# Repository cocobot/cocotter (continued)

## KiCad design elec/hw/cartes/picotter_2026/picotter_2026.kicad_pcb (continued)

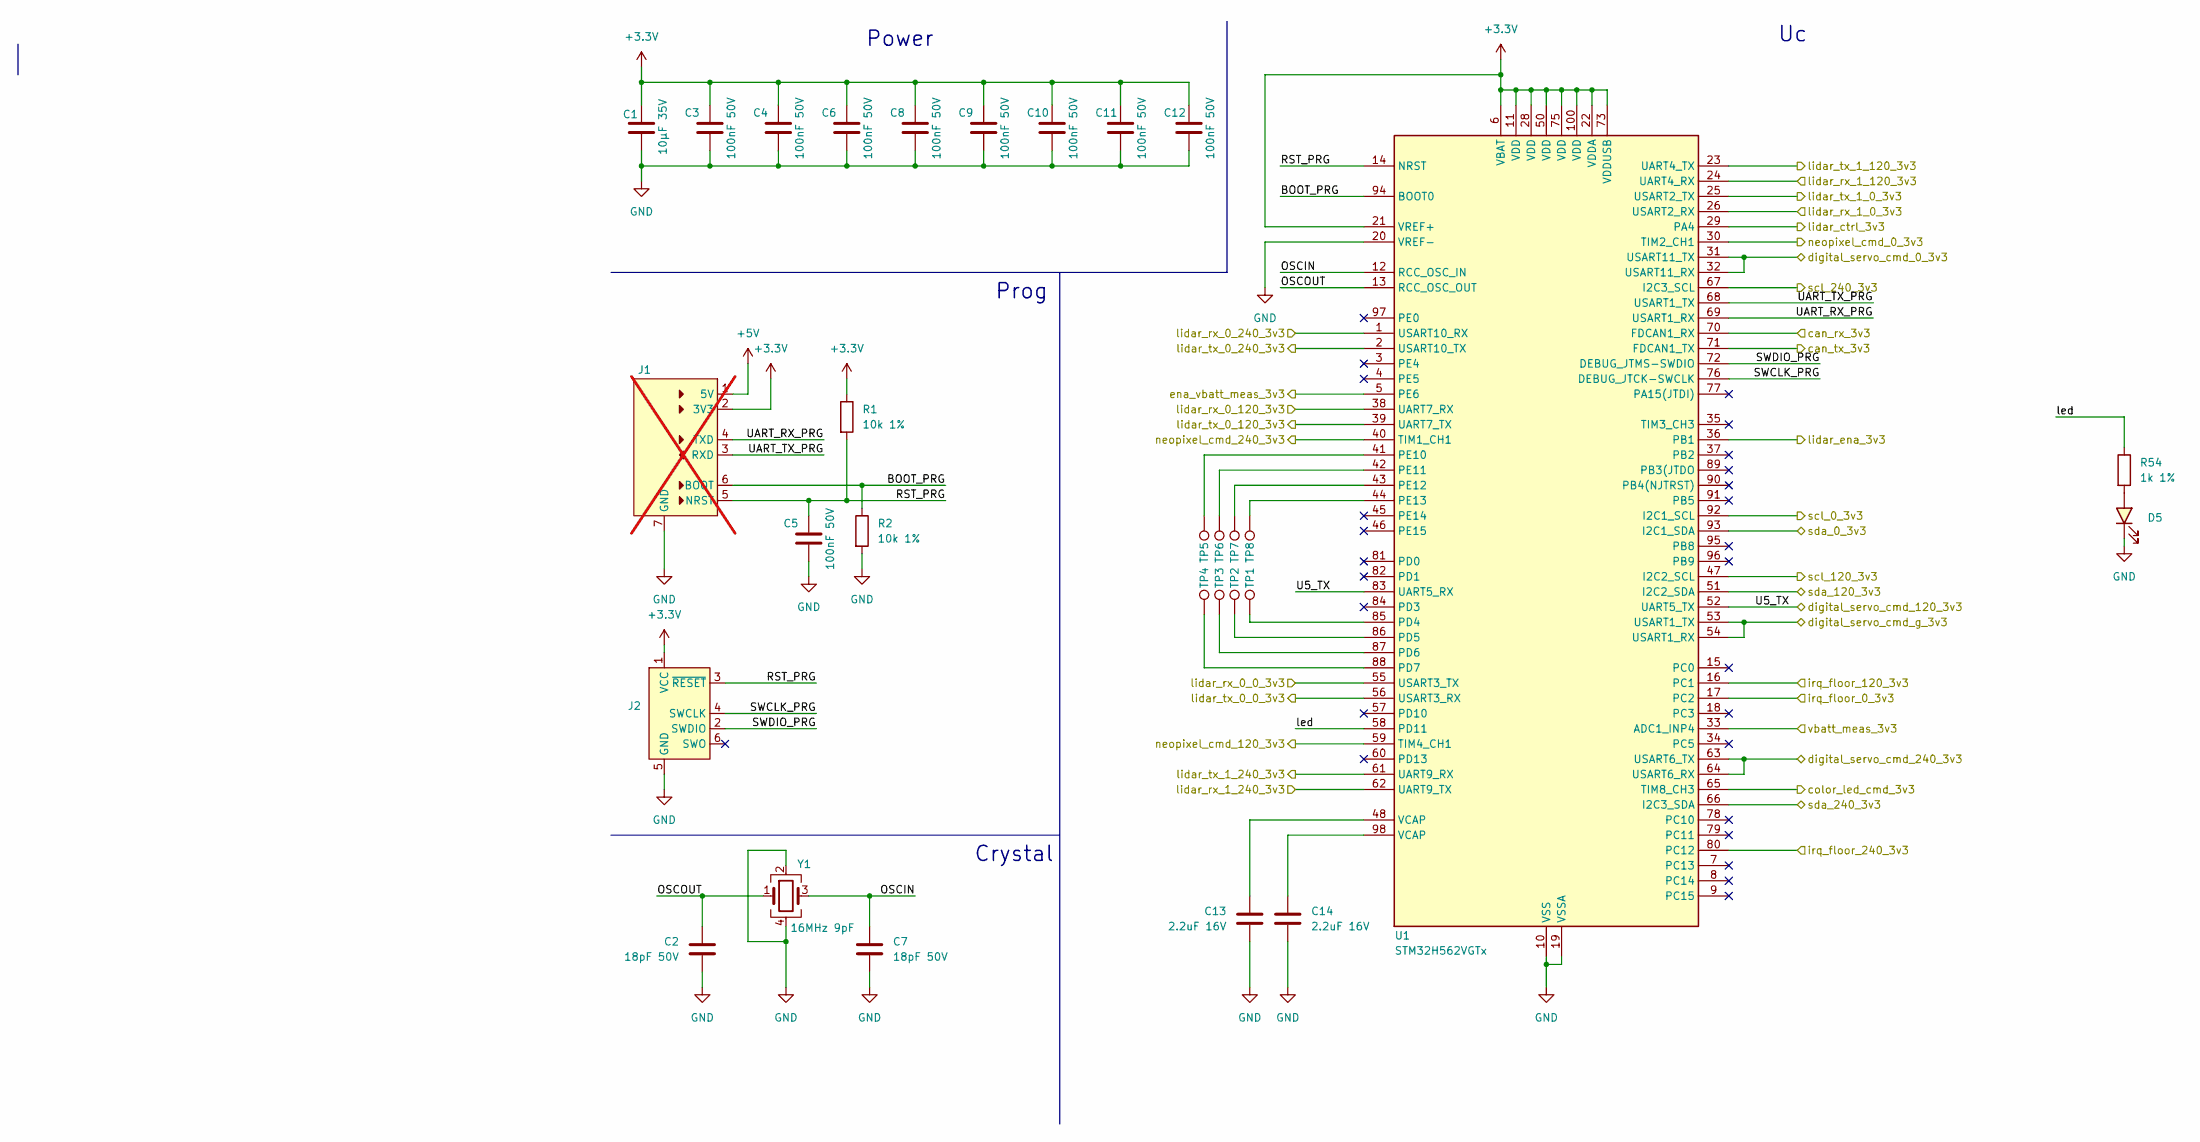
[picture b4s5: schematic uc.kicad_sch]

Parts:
C1: 10µF 35V; C_1206_3216Metric; jlcpcb C454102
C2, C7: 18pF 50V; C_0603_1608Metric; JLCPCB Part # C5137620
C3, C4, C5, C6, C8, C9, C10, C11, C12: 100nF 50V; C_0603_1608Metric; JLCPCB Part # C14663
C13, C14: 2.2uF 16V; C_0603_1608Metric; JLCPCB Part # C23630
D5: green, 0603; LED_0603_1608Metric; DIGIKEY_REF 3147-B19Y1UYG-20C000313U1930CT-ND
J1: eps32_uart_programmer; JLCPCB Part # C492406; not fitted
J2: Conn_ARM_SWD_TagConnect_TC2030; Tag-Connect_TC2030-IDC-FP_2x03_P1.27mm_Vertical
R1, R2: 10k 1%; r0603_reflow; mouser 603-RC0603FR-10100KL
R54: 1k 1%; r0603_reflow; mouser 603-RC0603FR-10100KL
TP1, TP2, TP3, TP4, TP5, TP6, TP7, TP8: TestPoint; testpoint-THT-0.5mm
U1: STM32H562VGTx; LQFP-100_14x14mm_P0.5mm
Y1: 16MHz 9pF; Crystal_SMD_3225-4Pin_3.2x2.5mm; JLCPCB Part # C13738

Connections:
+3.3V: C1.1, C3.1, C4.1, C6.1, C8.1, C9.1, C10.1, C11.1, C12.1, J1.2 (3V3), J2.1 (VCC), R1.1, U1.6 (VBAT), U1.11 (VDD), U1.21 (VREF+), U1.22 (VDDA), U1.28 (VDD), U1.50 (VDD), U1.73 (VDDUSB), U1.75 (VDD), U1.100 (VDD); also elsewhere on the board
+5V: J1.1 (5V); also elsewhere on the board
/Side 0/color_led_cmd_3v3: U1.65 (TIM8_CH3); also elsewhere on the board
/Side 0/digital_servo_cmd_3v3: U1.31 (USART11_TX), U1.32 (USART11_RX); also elsewhere on the board
/Side 0/digital_servo_cmd_g_3v3: U1.53 (USART1_TX), U1.54 (USART1_RX); also elsewhere on the board
/Side 0/irq_floor_3v3: U1.17 (PC2); also elsewhere on the board
/Side 0/lidar_ctrl_3v3: U1.29 (PA4); also elsewhere on the board
/Side 0/lidar_rx_0_3v3: U1.55 (USART3_TX); also elsewhere on the board
/Side 0/lidar_rx_1_3v3: U1.26 (USART2_RX); also elsewhere on the board
/Side 0/lidar_tx_0_3v3: U1.56 (USART3_RX); also elsewhere on the board
/Side 0/lidar_tx_1_3v3: U1.25 (USART2_TX); also elsewhere on the board
/Side 0/neopixel_cmd_3v3: U1.30 (TIM2_CH1); also elsewhere on the board
/Side 0/scl_3v3: U1.92 (I2C1_SCL); also elsewhere on the board
/Side 0/sda_3v3: U1.93 (I2C1_SDA); also elsewhere on the board
/Side 120/digital_servo_cmd_3v3: U1.52 (UART5_TX), U1.83 (UART5_RX); also elsewhere on the board
/Side 120/irq_floor_3v3: U1.16 (PC1); also elsewhere on the board
/Side 120/lidar_rx_0_3v3: U1.38 (UART7_RX); also elsewhere on the board
/Side 120/lidar_rx_1_3v3: U1.24 (UART4_RX); also elsewhere on the board
/Side 120/lidar_tx_0_3v3: U1.39 (UART7_TX); also elsewhere on the board
/Side 120/lidar_tx_1_3v3: U1.23 (UART4_TX); also elsewhere on the board
/Side 120/neopixel_cmd_3v3: U1.59 (TIM4_CH1); also elsewhere on the board
/Side 120/scl_3v3: U1.47 (I2C2_SCL); also elsewhere on the board
/Side 120/sda_3v3: U1.51 (I2C2_SDA); also elsewhere on the board
/Side 240/digital_servo_cmd_3v3: U1.63 (USART6_TX), U1.64 (USART6_RX); also elsewhere on the board
/Side 240/irq_floor_3v3: U1.80 (PC12); also elsewhere on the board
/Side 240/lidar_rx_0_3v3: U1.1 (USART10_RX); also elsewhere on the board
/Side 240/lidar_rx_1_3v3: U1.62 (UART9_TX); also elsewhere on the board
/Side 240/lidar_tx_0_3v3: U1.2 (USART10_TX); also elsewhere on the board
/Side 240/lidar_tx_1_3v3: U1.61 (UART9_RX); also elsewhere on the board
/Side 240/neopixel_cmd_3v3: U1.40 (TIM1_CH1); also elsewhere on the board
/Side 240/scl_3v3: U1.67 (I2C3_SCL); also elsewhere on the board
/Side 240/sda_3v3: U1.66 (I2C3_SDA); also elsewhere on the board
/com/can_rx_3v3: U1.70 (FDCAN1_RX); also elsewhere on the board
/com/can_tx_3v3: U1.71 (FDCAN1_TX); also elsewhere on the board
/power/ena_vbatt_meas_3v3: U1.5 (PE6); also elsewhere on the board
/power/lidar_ena_3v3: U1.36 (PB1); also elsewhere on the board
/power/vbatt_meas_3v3: U1.33 (ADC1_INP4); also elsewhere on the board
/uc/BOOT_PRG: J1.6 (BOOT), R2.1, U1.94 (BOOT0)
/uc/OSCIN: C7.1, U1.12 (RCC_OSC_IN), Y1.3
/uc/OSCOUT: C2.1, U1.13 (RCC_OSC_OUT), Y1.1
/uc/RST_PRG: C5.1, J1.5 (NRST), J2.3 (~RESET), R1.2, U1.14 (NRST)
/uc/SWCLK_PRG: J2.4 (SWCLK), U1.76 (DEBUG_JTCK-SWCLK)
/uc/SWDIO_PRG: J2.2 (SWDIO), U1.72 (DEBUG_JTMS-SWDIO)
/uc/UART_RX_PRG: J1.4 (TXD), U1.69 (USART1_RX)
/uc/UART_TX_PRG: J1.3 (RXD), U1.68 (USART1_TX)
/uc/led: R54.1, U1.58 (PD11)
GND: C1.2, C2.2, C3.2, C4.2, C5.2, C6.2, C7.2, C8.2, C9.2, C10.2, C11.2, C12.2, C13.2, C14.2, D5.C, J1.7 (GND), J2.5 (GND), R2.2, U1.10 (VSS), U1.19 (VSSA), U1.20 (VREF-), U1.27 (VSS), U1.49 (VSS), U1.74 (VSS), U1.99 (VSS), Y1.2, Y1.4; also elsewhere on the board
unnamed: C13.1, U1.48 (VCAP)
unnamed: C14.1, U1.98 (VCAP)
unnamed: D5.A, R54.2
unnamed: TP1.1, U1.85 (PD4)
unnamed: TP2.1, U1.86 (PD5)
unnamed: TP3.1, U1.87 (PD6)
unnamed: TP4.1, U1.88 (PD7)
unnamed: TP5.1, U1.41 (PE10)
unnamed: TP6.1, U1.42 (PE11)
unnamed: TP7.1, U1.43 (PE12)
unnamed: TP8.1, U1.44 (PE13)

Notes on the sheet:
Prog
Crystal
Power

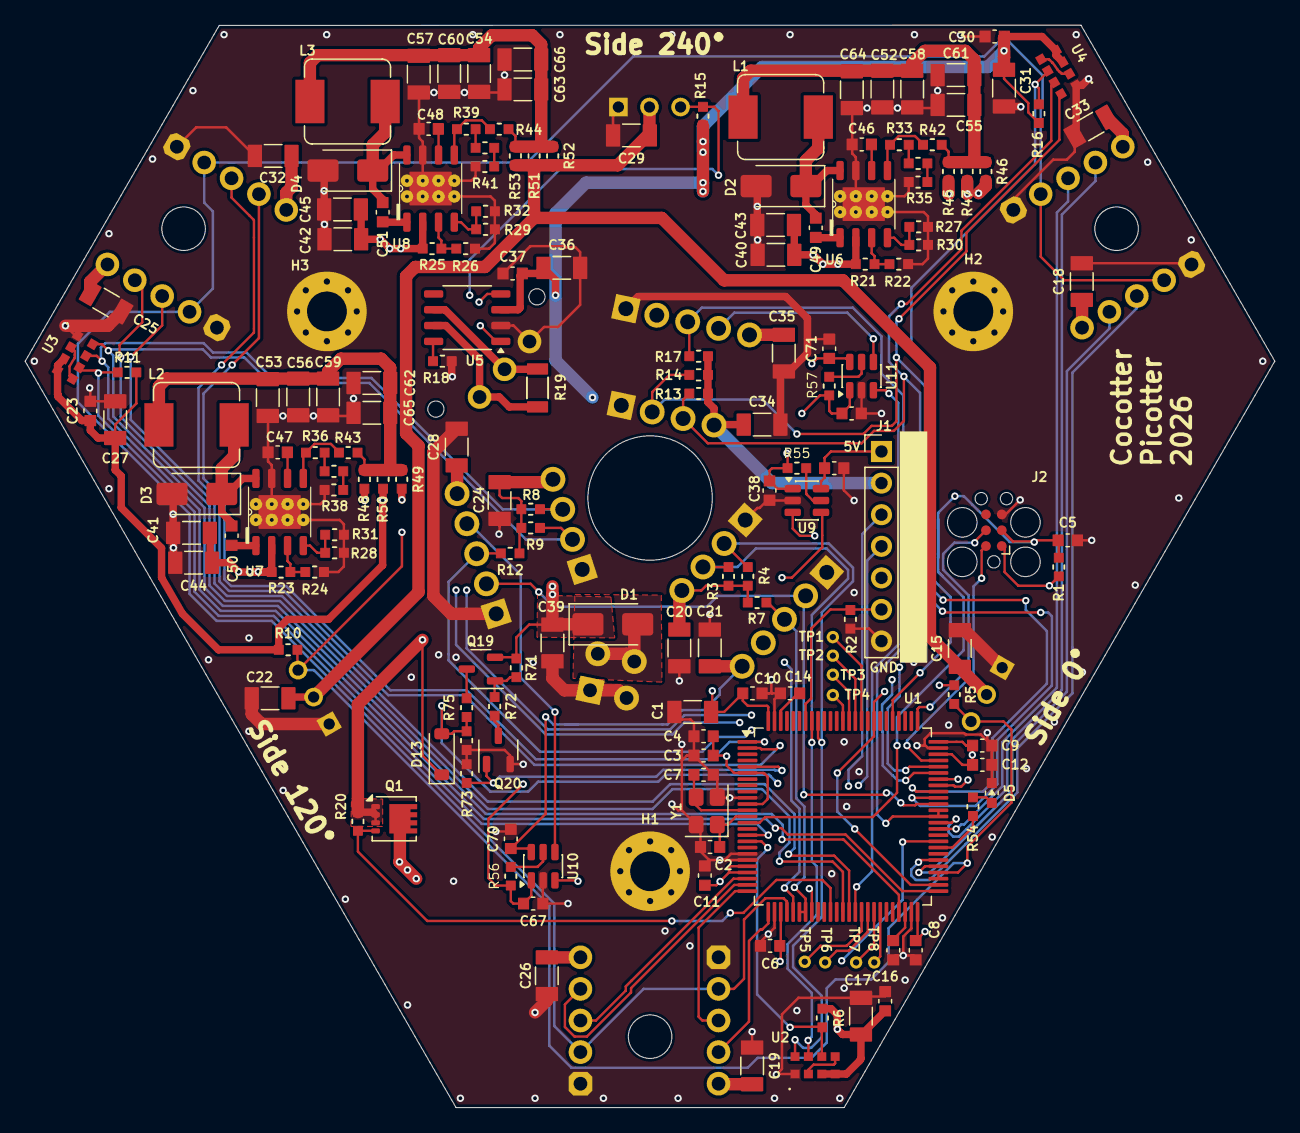
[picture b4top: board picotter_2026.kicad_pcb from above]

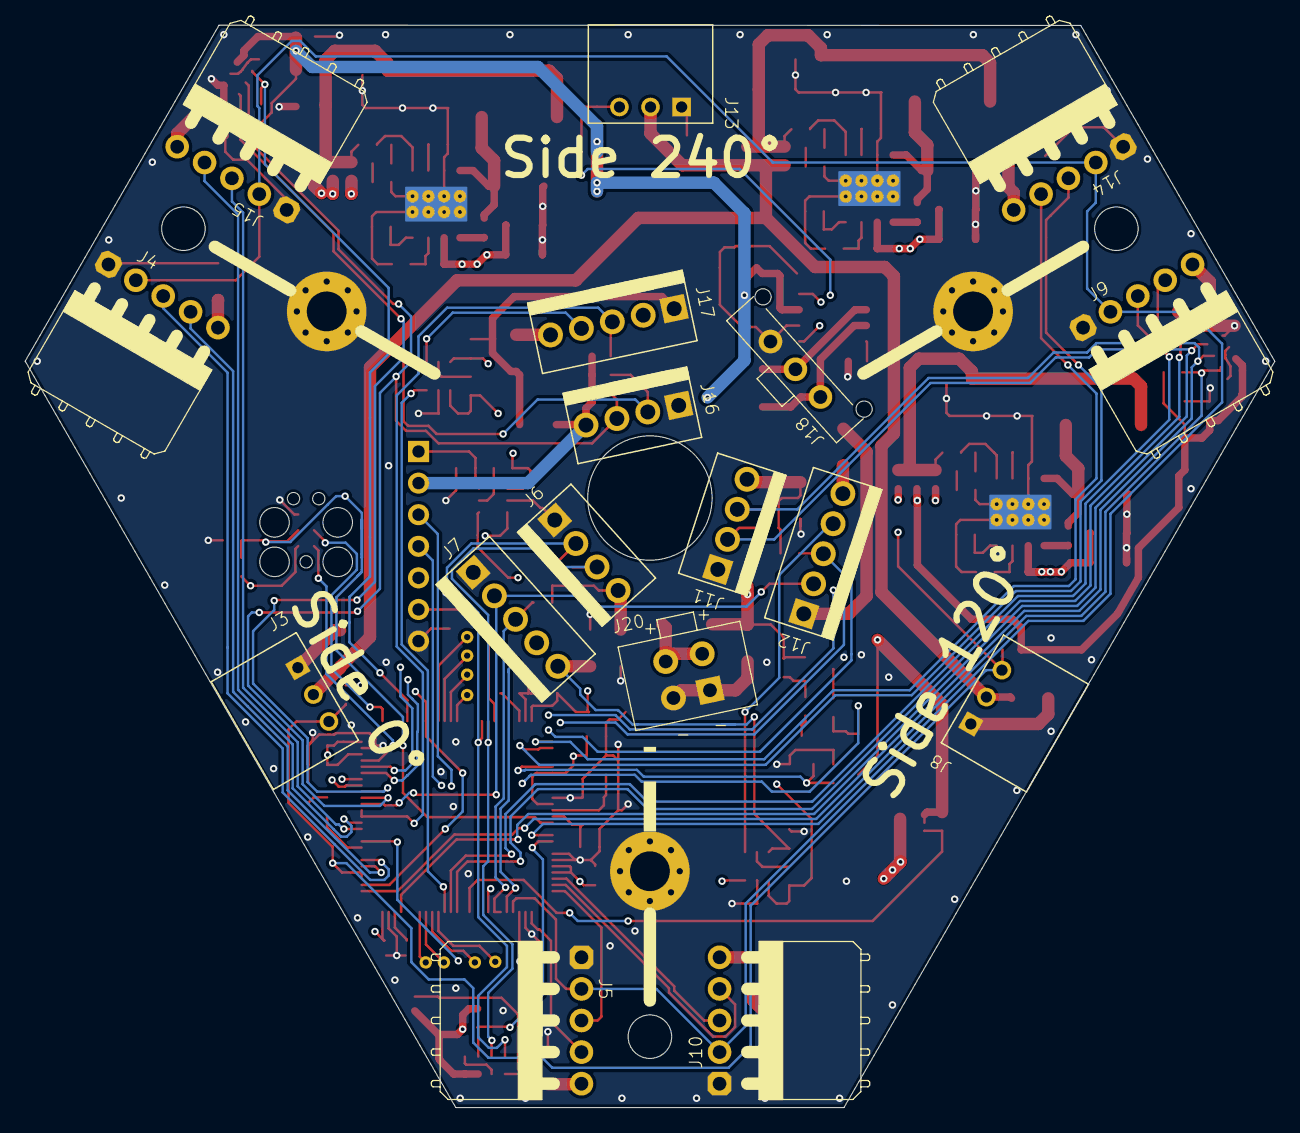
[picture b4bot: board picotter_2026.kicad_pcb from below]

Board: 4 copper layers, 100.5 x 87.0 mm, 187 parts (17 on the bottom side), 104 nets.

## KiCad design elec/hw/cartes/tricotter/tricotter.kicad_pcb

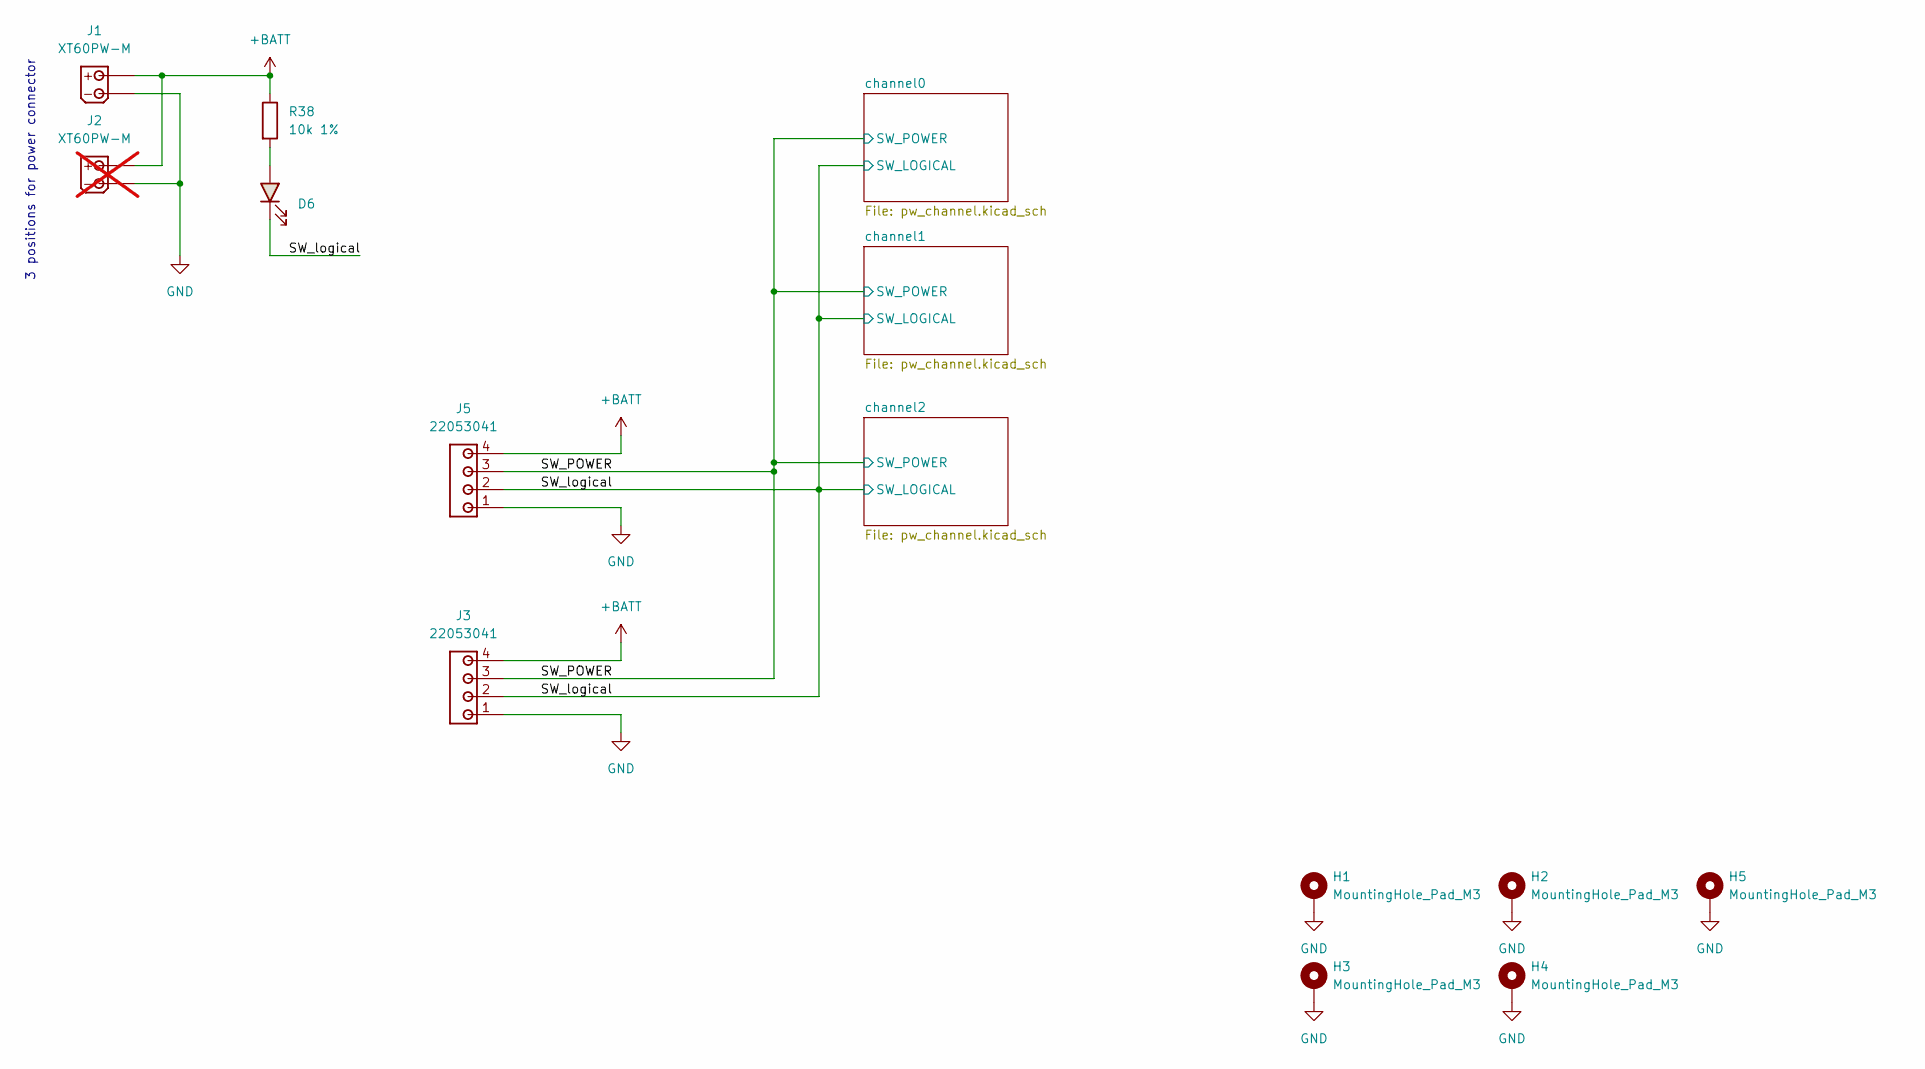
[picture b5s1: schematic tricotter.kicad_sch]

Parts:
D6: white, 0603; LED_0603_1608Metric; JLCPCB Part # C2290
H1, H2, H3, H4, H5: MountingHole_Pad_M3; MountingHole_3.2mm_M3_Pad_Via
J1: XT60PW-M; JLCPCB Part # C98732
J2: XT60PW-M; JLCPCB Part # C98732; not fitted
J3, J5: 22053041; JLCPCB Part # C5271241
R38: 10k 1%; r0603_reflow; mouser 603-RC0603FR-10100KL

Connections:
+BATT: J1.P, J2.P, J3.4, J5.4, R38.1; also elsewhere on the board
/SW_POWER: J3.3, J5.3; also elsewhere on the board
/SW_logical: D6.C, J3.2, J5.2; also elsewhere on the board
GND: H1.1, H2.1, H3.1, H4.1, H5.1, J1.M, J2.M, J3.1, J5.1; also elsewhere on the board
unnamed: D6.A, R38.2

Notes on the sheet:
3 positions for power connector

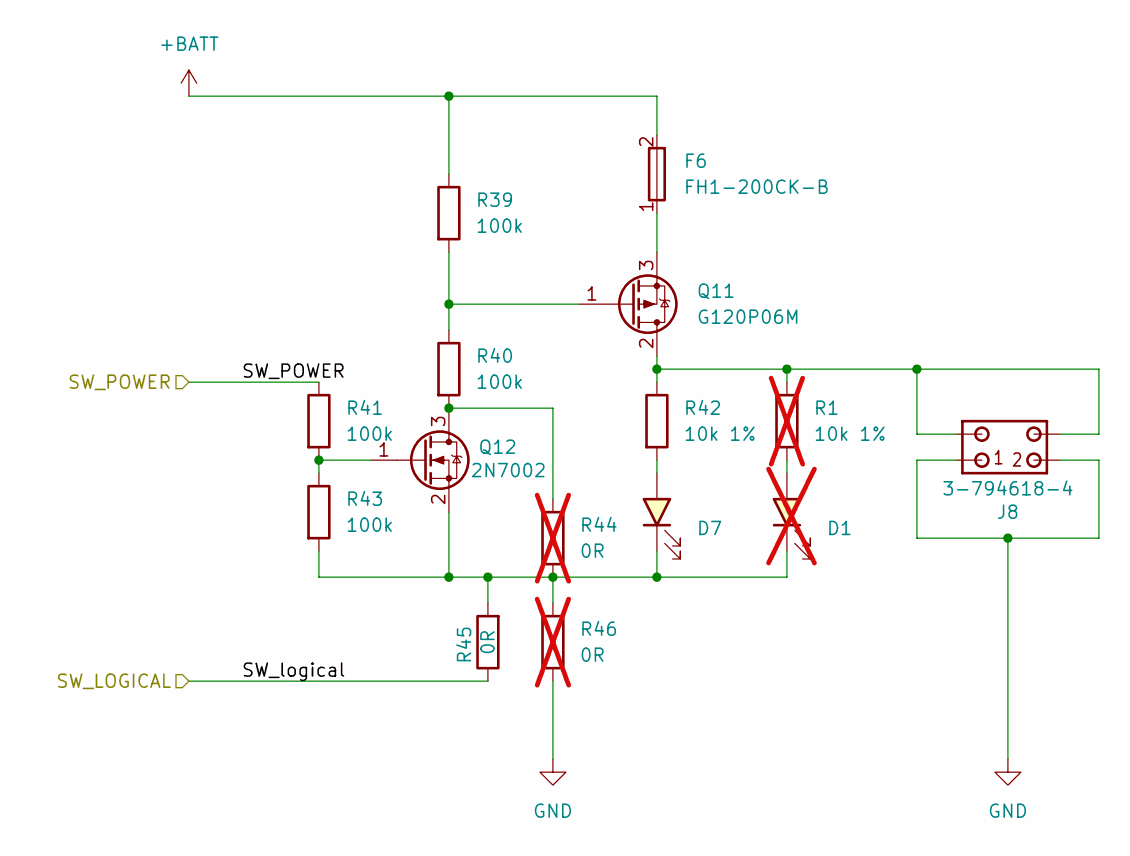
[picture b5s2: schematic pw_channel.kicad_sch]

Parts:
D1: green, 0603; LED_0603_1608Metric; DIGIKEY_REF 3147-B19Y1UYG-20C000313U1930CT-ND; not fitted
D7: green, 0603; LED_0603_1608Metric; DIGIKEY_REF 3147-B19Y1UYG-20C000313U1930CT-ND
F6: FH1-200CK-B; FUSEHOLDER_5x20mm; JLCPCB Part # C136374
J8: 3-794618-4
Q11: G120P06M; TO-263-2-GOFORD; JLCPCB Part # C5162393
Q12: 2N7002; SOT-23-3; JLCPCB Part # C8545
R1: 10k 1%; r0603_reflow; mouser 603-RC0603FR-10100KL; not fitted
R39, R40, R41, R43: 100k; r0603_reflow; mouser 603-RC0603FR-10100KL
R42: 10k 1%; r0603_reflow; mouser 603-RC0603FR-10100KL
R44, R46: 0R; r0603_reflow; JLCPCB Part # C431718; not fitted
R45: 0R; r0603_reflow; JLCPCB Part # C431718

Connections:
+BATT: F6.2, R39.1; also elsewhere on the board
/SW_POWER: R41.1; also elsewhere on the board
/SW_logical: R45.1; also elsewhere on the board
GND: J8.1, J8.2, R46.2; also elsewhere on the board
unnamed: D1.A, R1.2
unnamed: D7.A, R42.2
unnamed: J8.3, J8.4, Q11.2 (D), R1.1, R42.1
unnamed: Q11.1 (G), R39.2, R40.1
unnamed: F6.1, Q11.3 (S)
unnamed: Q12.3 (D), R40.2, R44.1
unnamed: Q12.1 (G), R41.2, R43.1
unnamed: D1.C, D7.C, Q12.2 (S), R43.2, R44.2, R45.2, R46.1

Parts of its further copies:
D2, D3: green, 0603; LED_0603_1608Metric; DIGIKEY_REF 3147-B19Y1UYG-20C000313U1930CT-ND; not fitted
D8, D9: green, 0603; LED_0603_1608Metric; DIGIKEY_REF 3147-B19Y1UYG-20C000313U1930CT-ND
F7, F8: FH1-200CK-B; FUSEHOLDER_5x20mm; JLCPCB Part # C136374
J9, J10: 3-794618-4
Q13, Q15: G120P06M; TO-263-2-GOFORD; JLCPCB Part # C5162393
Q14, Q16: 2N7002; SOT-23-3; JLCPCB Part # C8545
R2, R3: 10k 1%; r0603_reflow; mouser 603-RC0603FR-10100KL; not fitted
R47, R48, R49, R51, R55, R56, R57, R59: 100k; r0603_reflow; mouser 603-RC0603FR-10100KL
R50, R58: 10k 1%; r0603_reflow; mouser 603-RC0603FR-10100KL
R52, R54, R60, R62: 0R; r0603_reflow; JLCPCB Part # C431718; not fitted
R53, R61: 0R; r0603_reflow; JLCPCB Part # C431718

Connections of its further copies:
+BATT: F7.2, F8.2, R47.1, R55.1; also elsewhere on the board
/SW_POWER: R49.1, R57.1; also elsewhere on the board
/SW_logical: R53.1, R61.1; also elsewhere on the board
GND: J9.1, J9.2, J10.1, J10.2, R54.2, R62.2; also elsewhere on the board
unnamed: D2.A, R2.2
unnamed: D3.A, R3.2
unnamed: D8.A, R50.2
unnamed: D9.A, R58.2
unnamed: J9.3, J9.4, Q13.2 (D), R2.1, R50.1
unnamed: Q13.1 (G), R47.2, R48.1
unnamed: F7.1, Q13.3 (S)
unnamed: Q14.3 (D), R48.2, R52.1
unnamed: Q14.1 (G), R49.2, R51.1
unnamed: D2.C, D8.C, Q14.2 (S), R51.2, R52.2, R53.2, R54.1
unnamed: J10.3, J10.4, Q15.2 (D), R3.1, R58.1
unnamed: Q15.1 (G), R55.2, R56.1
unnamed: F8.1, Q15.3 (S)
unnamed: Q16.3 (D), R56.2, R60.1
unnamed: Q16.1 (G), R57.2, R59.1
unnamed: D3.C, D9.C, Q16.2 (S), R59.2, R60.2, R61.2, R62.1

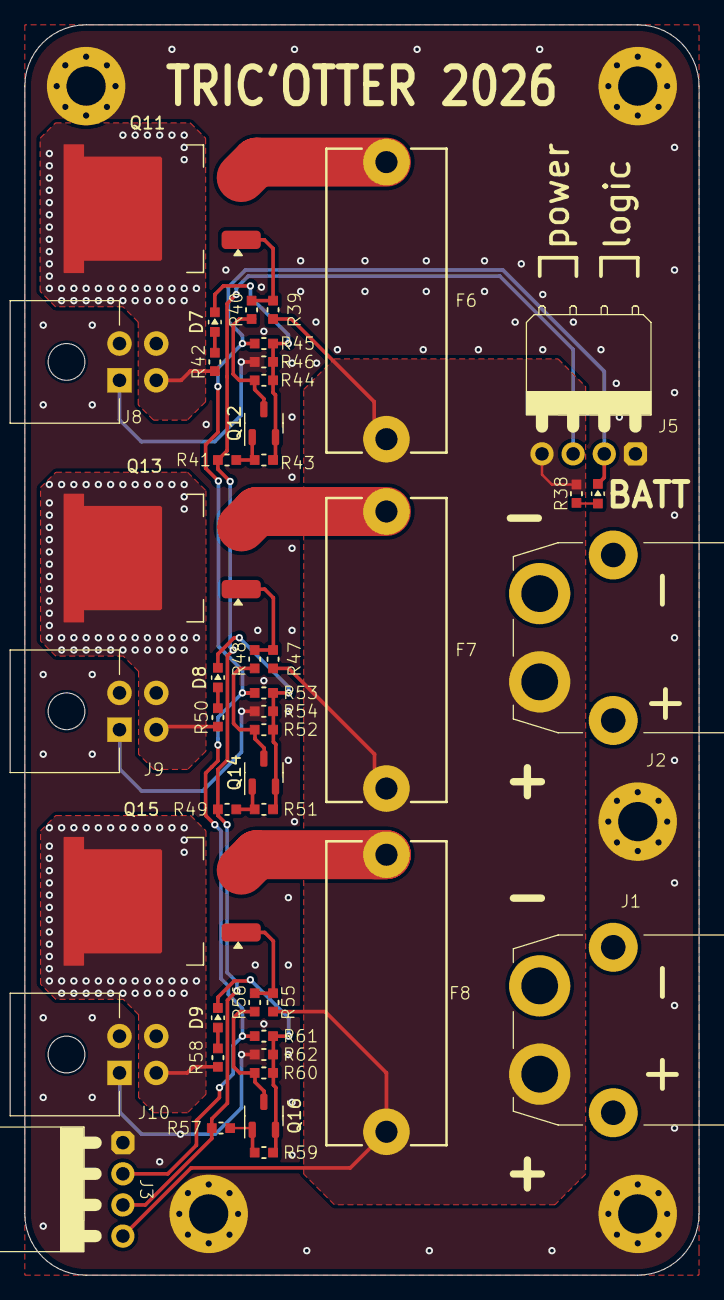
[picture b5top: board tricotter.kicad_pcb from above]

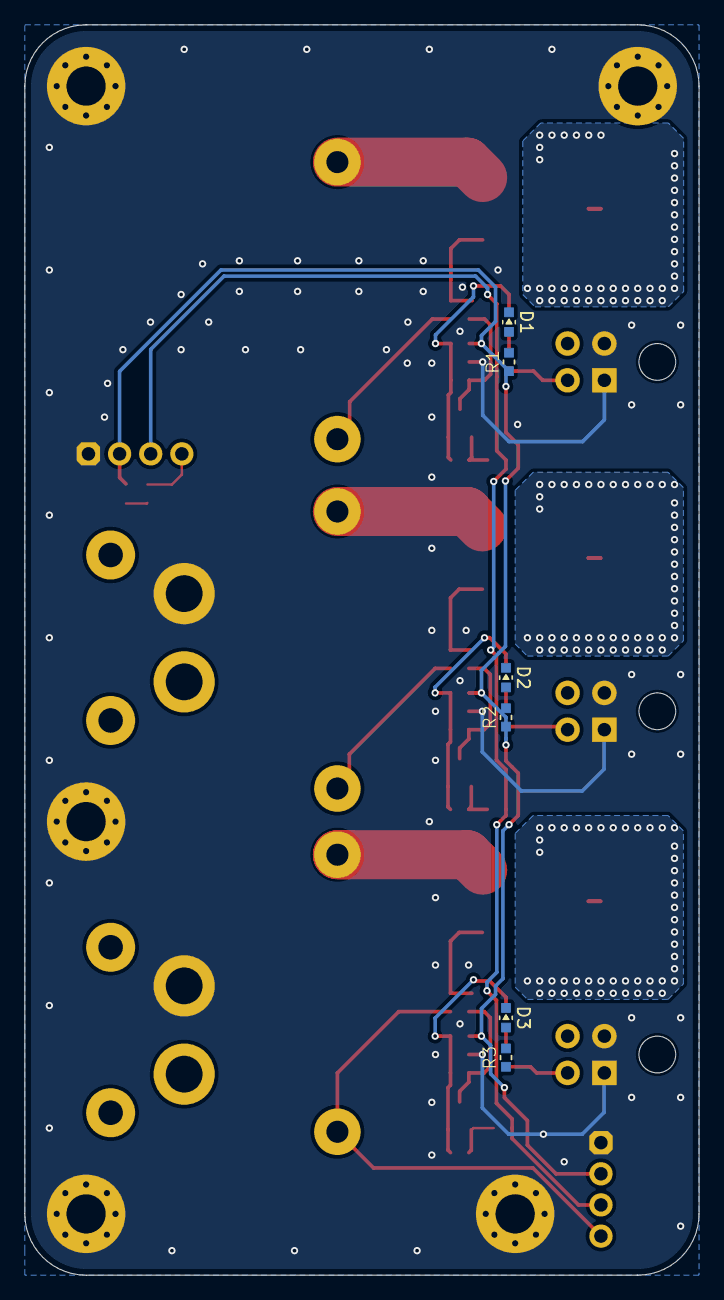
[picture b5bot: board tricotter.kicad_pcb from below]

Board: 2 copper layers, 55.0 x 102.0 mm, 56 parts (6 on the bottom side), 29 nets.

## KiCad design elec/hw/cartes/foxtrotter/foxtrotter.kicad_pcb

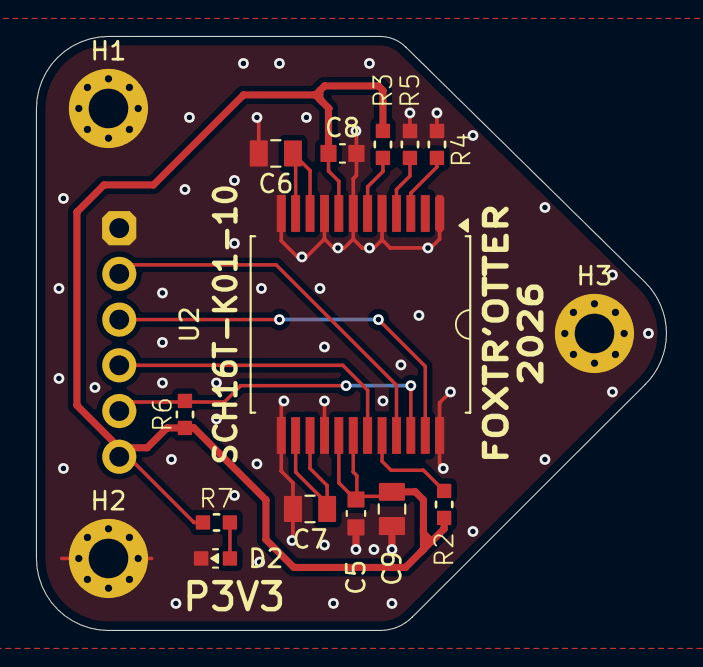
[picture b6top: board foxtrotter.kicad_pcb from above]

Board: 2 copper layers, 35.0 x 33.0 mm, 17 parts (1 on the bottom side), 13 nets.

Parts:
C5, C8: 100nF 50V; C_0603_1608Metric
C6: 10µF 25V; C_0805_2012Metric
C7, C9: 1µF 50V; C_0805_2012Metric
D2: green, 0603; LED_0603_1608Metric
H1, H2, H3: MountingHole_Pad_M2; MountingHole_2.2mm_M2_Pad_Via
J1: 22053061
R2, R6: 91k 1%; r0603_reflow
R3: 10k 1%; r0603_reflow
R4, R5: 0R; r0603_reflow
R7: 330R; r0603_reflow
U2: SCH16T-K01-10; SCH16T

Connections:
+3V3: C5.1, C8.1, C9.1, J1.6, R2.1, R3.1, R6.1, R7.1, U2.8 (V3P3), U2.17 (V3P3), U2.18 (VddIO)
/gyro_miso_3v3: J1.4, U2.19 (MISO)
/gyro_mosi_3v3: J1.3, U2.23 (MOSI)
/gyro_sck_3v3: J1.2, U2.21 (SCK)
//gyro_cs_3v3: J1.5, R6.2, U2.22 (/CS)
GND: C5.2, C6.2, C7.2, C8.2, C9.2, D2.C, H1.1, H2.1, H3.1, J1.1, R4.2, R5.2, U2.1 (HEATSINK), U2.5 (RSVD(GND)), U2.7 (RSVD(GND)), U2.9 (GND), U2.12 (GND), U2.13 (GND), U2.16 (GND), U2.24 (HEATSINK)
unnamed: D2.A, R7.2
unnamed: R2.2, U2.20 (DRY/SYNC)
unnamed: R5.1, U2.4 (TA8)
unnamed: R4.1, U2.3 (TA9)
unnamed: C6.1, U2.10 (VREGA2), U2.11 (VREGA)
unnamed: C7.1, U2.14 (VREGD2), U2.15 (VREGD)
unnamed: R3.2, U2.6 (/EXT_RESET)

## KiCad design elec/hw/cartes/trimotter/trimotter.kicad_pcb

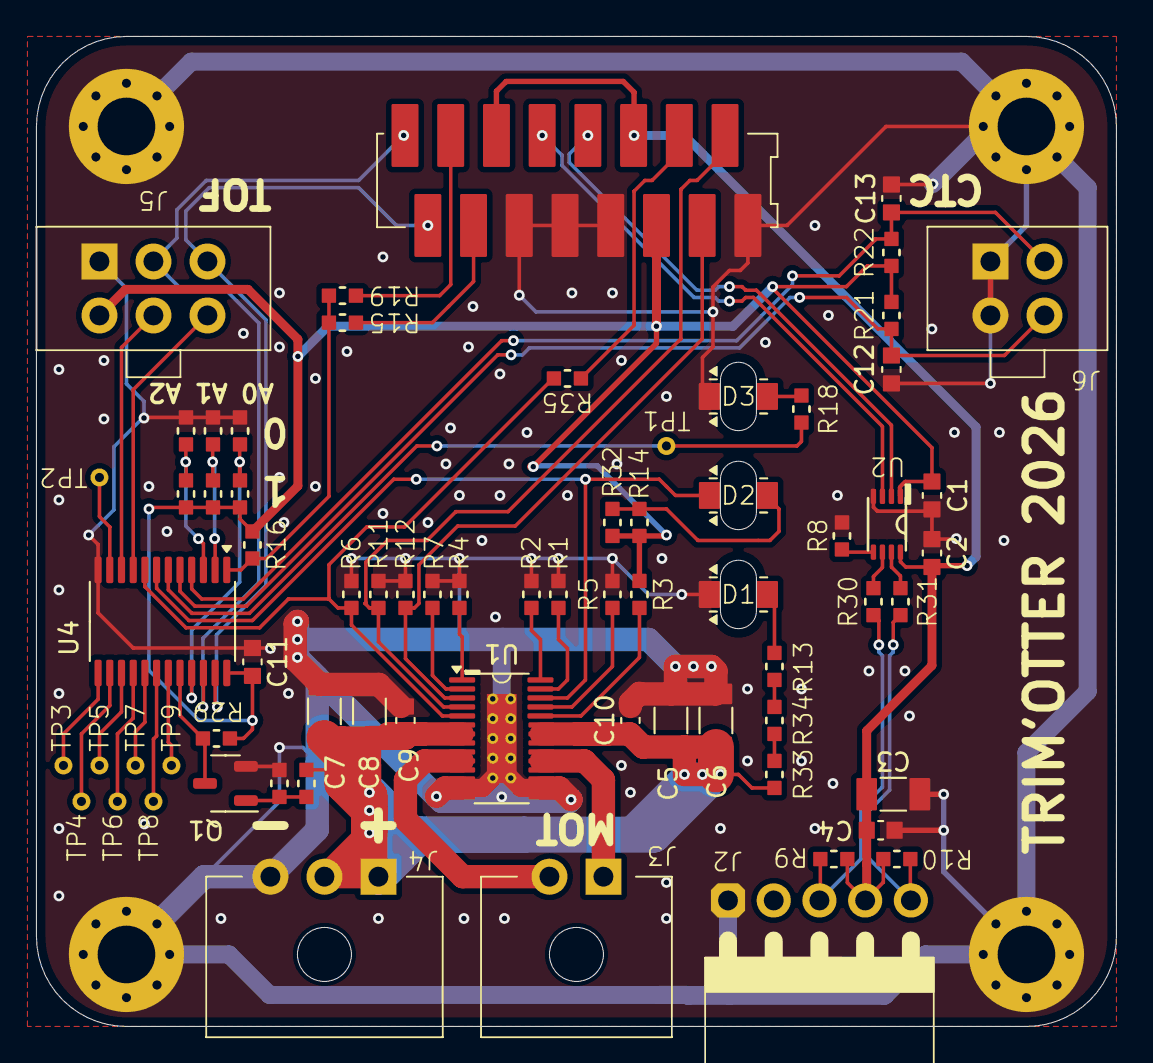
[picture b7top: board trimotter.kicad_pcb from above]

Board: 2 copper layers, 60.0 x 55.0 mm, 74 parts (0 on the bottom side), 52 nets.

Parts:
C1, C2, C4, C9, C10, C11, C12, C13: 100nF 50V; C_0603_1608Metric
C3, C5, C6, C7, C8: 47µF 10V; C_1206_3216Metric
D1, D3: green, 1206; 24-21-1206_reverse_mount
D2: red, 1206; 24-21-1206_reverse_mount
H1, H2, H3, H4: MountingHole_Pad_M3; MountingHole_3.2mm_M3_Pad_Via
J1: 1-188275-6
J2: 22053051
J3: 2-1445055-2
J4: 2-1445055-3
J5: 3-794630-6
J6: 3-794630-4
Q1: 2N7002; SOT-23-3
R1, R2, R3, R4, R7, R15, R17, R19, R24, R26, R30, R31, R35: 0R; r0603_reflow
R5: 1k3 1%; r0603_reflow
R6, R8, R11, R12, R16, R20, R21, R22, R23, R25, R27, R28, R29: 100k; r0603_reflow
R9, R10, R13, R33, R34: 3k3 1%; r0603_reflow
R14, R18, R32: 1k 1%; r0603_reflow
TP1, TP2, TP3, TP4, TP5, TP6, TP7, TP8, TP9: TestPoint; testpoint-THT-0.5mm
U1: DRV8243HQDGQRQ1; HVSSOP-28-1EP_3x7mm_P0.5mm_EP1.65x5mm_ThermalVias
U2: SN74LVC2T45DCU; VSSOP-8-DCU
U4: PCA9535PW; TSSOP-24_4.4x7.8mm_P0.65mm

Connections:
+3V3: C1.1, C11.1, J1.5 (P3V3), J5.4, R3.1, R14.2, R16.1, R20.1, R21.1, R22.1, R23.1, R25.1, R29.1, R32.2, U2.1 (VCCA), U4.24 (VDD)
/brake_mot_3v3: R6.1, R35.2, U1.5 (DRVOFF), U4.8 (IO0_4)
/ctc_left_3v3: C13.1, J6.2, R22.2, U4.4 (IO0_0)
/ctc_right_3v3: C12.1, J6.4, R21.2, U4.5 (IO0_1)
/dir_3v3: J1.3 (dir_3v3), R12.1, U1.3 (PH/IN2)
/enable_tof_3v3: J5.5, U4.10 (IO0_6)
/encoder_A_3v3: J1.8 (encod_A_3v3), U2.2 (A1)
/encoder_A_5v: J2.3 (CH_A), R9.2, R30.2
/encoder_B_3v3: J1.10 (encod_B_3v3), U2.3 (A2)
/encoder_B_5v: J2.5 (CH_B), R10.2, R31.2
/irq0_3v3: J1.13 (MISO_3v3), R15.1
/irq1_3v3: J1.14 (MOSI_3v3), R19.1
/led_com_3v3: R18.1, TP1.1, U4.6 (IO0_2)
/mot_N: J3.1, U1.18 (OUT2), U1.19 (OUT2), U1.20 (OUT2)
/mot_P: J3.2, U1.9 (OUT1), U1.10 (OUT1), U1.11 (OUT1)
/nFAULT_3V3: D2.C, U1.26 (nFAULT), U4.7 (IO0_3)
/pwm_3v3: J1.2 (pwm_3v3), R11.1, U1.4 (EN/IN1)
/reset_tof_3v3: J5.6, U4.9 (IO0_5)
/scl_tof_3v3: J1.16 (nCS_3v3), J5.2, U4.22 (SCL)
/sda_tof_3v3: J1.15 (SCK_3v3), J5.3, U4.23 (SDA)
/vmot_absent_3v3: Q1.3 (D), R29.2, U4.20 (IO1_7)
GND: C1.2, C2.2, C3.2, C4.2, C5.2, C6.2, C7.2, C8.2, C9.2, C10.2, C11.2, C12.2, C13.2, D1.C, D3.C, H1.1, H2.1, H3.1, H4.1, J1.1 (GND), J1.7 (GND), J1.9 (GND), J1.11 (GND), J2.1 (GND), J4.3, J5.1, J6.1, J6.3, Q1.2 (S), R1.2, R2.2, R4.2, R5.2, R6.2, R7.2, R8.2, R11.2, R12.2, R17.2, R24.2, R26.2, R28.2, U1.12 (GND), U1.13 (GND), U1.14 (GND), U1.15 (GND), U1.16 (GND), U1.17 (GND), U1.EP, U2.4 (GND), U4.12 (VSS)
unnamed: D1.A, R13.2
unnamed: D2.A, R14.1, R32.1
unnamed: D3.A, R18.2
unnamed: J1.4 (brake_3v3), R35.1
unnamed: Q1.1 (G), R27.2, R28.1
unnamed: R13.1, R34.2
unnamed: R33.2, R34.1
unnamed: R7.1, U1.2 (DIAG)
unnamed: R5.1, U1.25 (IPROPI)
unnamed: R2.1, U1.28 (ITRIP)
unnamed: R1.1, U1.27 (MODE)
unnamed: R4.1, U1.1 (SR)
unnamed: R3.2, U1.24 (nSLEEP)
unnamed: R31.1, U2.7 (B1)
unnamed: R30.1, U2.6 (B2)
unnamed: R8.1, U2.5 (DIR)
unnamed: R25.2, R26.1, U4.21 (A0)
unnamed: R23.2, R24.1, U4.2 (A1)
unnamed: R17.1, R20.2, U4.3 (A2)
unnamed: TP2.1, U4.11 (IO0_7)
unnamed: TP3.1, U4.13 (IO1_0)
unnamed: TP4.1, U4.14 (IO1_1)
unnamed: TP5.1, U4.15 (IO1_2)
unnamed: TP6.1, U4.16 (IO1_3)
unnamed: TP7.1, U4.17 (IO1_4)
unnamed: TP8.1, U4.18 (IO1_5)
unnamed: TP9.1, U4.19 (IO1_6)
unnamed: R15.2, R16.2, R19.2, U4.1 (~INT)
P5V: C2.1, C3.1, C4.1, J1.6 (P5V), J1.12 (P5V), J2.4 (VCC), R9.1, R10.1, U2.8 (VCCB)
VMOT: C5.1, C6.1, C7.1, C8.1, C9.1, C10.1, J4.1, J4.2, R27.1, R33.1, U1.6 (VM), U1.7 (VM), U1.8 (VM), U1.21 (VM), U1.22 (VM), U1.23 (VM)

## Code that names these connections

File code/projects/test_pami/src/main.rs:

use esp_idf_svc::hal::{adc, delay::TickType, gpio::{AnyInputPin, Level, PinDriver}, i2c::{I2cConfig, I2cDriver}, ledc::{config::TimerConfig, LedcDriver, LedcTimerDriver}, pcnt::PcntDriver, peripherals::Peripherals, spi, units::KiloHertz};

fn main()  {
    // It is necessary to call this function once. Otherwise some patches to the runtime
    // implemented by esp-idf-sys might not link properly. See https://github.com/esp-rs/esp-idf-template/issues/71
    esp_idf_svc::sys::link_patches();

    // Bind the log crate to the ESP Logging facilities
    esp_idf_svc::log::EspLogger::initialize_default();

    //init all the peripherals
    let peripherals = Peripherals::take().unwrap();
    let mut adc = adc::AdcDriver::new(peripherals.adc1, &adc::config::Config::new().calibration(true)).unwrap();
    let timer_motors = LedcTimerDriver::new(
        peripherals.ledc.timer0,
        &TimerConfig::default().frequency(KiloHertz(16).into()),
    ).unwrap();
    let mut i2c_driver = I2cDriver::new(peripherals.i2c0, peripherals.pins.gpio18, peripherals.pins.gpio17, &I2cConfig::new().baudrate(KiloHertz(100).into())).unwrap();
    let spi_driver = spi::SpiDriver::new(
        peripherals.spi2,
        peripherals.pins.gpio48,
        peripherals.pins.gpio36,
        Some(peripherals.pins.gpio35),
        &spi::SpiDriverConfig::new(),
    ).unwrap();
    
    let mut battery_level_input: adc::AdcChannelDriver<{ adc::attenuation::NONE }, _> = adc::AdcChannelDriver::new(peripherals.pins.gpio1).unwrap();
    let start_robot_input = PinDriver::input(peripherals.pins.gpio2).unwrap();
    let mut led_run_output = PinDriver::output(peripherals.pins.gpio4).unwrap();
    let mut led_com_output = PinDriver::output(peripherals.pins.gpio5).unwrap();
    let contact_left_input = PinDriver::input(peripherals.pins.gpio6).unwrap();
    let conf3_input = PinDriver::input(peripherals.pins.gpio7).unwrap();
    let tof_irq_input = PinDriver::input(peripherals.pins.gpio8).unwrap();
    let mut current_right_motor_input: adc::AdcChannelDriver<{ adc::attenuation::NONE }, _> = adc::AdcChannelDriver::new(peripherals.pins.gpio9).unwrap();
    let mut current_left_motor_input: adc::AdcChannelDriver<{ adc::attenuation::NONE }, _> = adc::AdcChannelDriver::new(peripherals.pins.gpio10).unwrap();
    let io_irq_input = PinDriver::input(peripherals.pins.gpio11).unwrap();
    let mut right_motor_dir_output = PinDriver::output(peripherals.pins.gpio12).unwrap();
    let mut right_motor_pwm = LedcDriver::new(
        peripherals.ledc.channel0,
        &timer_motors,
        peripherals.pins.gpio13,
    ).unwrap();
    let mut left_motor_dir_output = PinDriver::output(peripherals.pins.gpio14).unwrap();
    let emergency_stop_input = PinDriver::input(peripherals.pins.gpio15).unwrap();
    let mut enable_front_tof  = PinDriver::output(peripherals.pins.gpio16).unwrap();
    let mut left_motor_pwm = LedcDriver::new(
        peripherals.ledc.channel1,
        &timer_motors,
        peripherals.pins.gpio21,
    ).unwrap();
    let mut gyro_spi = spi::SpiDeviceDriver::new(
        spi_driver, 
        Some(peripherals.pins.gpio37), 
        &spi::config::Config::new().baudrate(KiloHertz(100).into()).data_mode(spi::config::MODE_3)
    ).unwrap();
    let gyro_irq_input = PinDriver::input(peripherals.pins.gpio38).unwrap();
    let left_encoder = PcntDriver::new(
        peripherals.pcnt0,
        Some(peripherals.pins.gpio39),
        Some(peripherals.pins.gpio40),
        Option::<AnyInputPin>::None,
        Option::<AnyInputPin>::None,
    ).unwrap();
    let right_encoder = PcntDriver::new(
        peripherals.pcnt1,
        Some(peripherals.pins.gpio42),
        Some(peripherals.pins.gpio41),
        Option::<AnyInputPin>::None,
        Option::<AnyInputPin>::None,
    ).unwrap();
    //TODO QUAD ENC
    let contact_right_input = PinDriver::input(peripherals.pins.gpio47).unwrap();

    let mut loop_counter = 0;
    loop {
        log::info!("Batery ADC value: {}", adc.read(&mut battery_level_input).unwrap());
        log::info!("Start Robot input: {:?}", start_robot_input.get_level());
        led_run_output.set_level(if loop_counter % 3 == 0 { Level::High } else { Level::Low }).unwrap();
        led_com_output.set_level(if loop_counter % 3 == 1 { Level::Low } else { Level::High }).unwrap();
        log::info!("Contact left: {:?}", contact_left_input.get_level());
        log::info!("Conf3: {:?}", conf3_input.get_level());
        log::info!("TOF IRQ: {:?}", tof_irq_input.get_level());
        log::info!("Current right motor ADC value: {}", adc.read(&mut current_right_motor_input).unwrap());
        log::info!("Current left motor ADC value: {}", adc.read(&mut current_left_motor_input).unwrap());
        log::info!("IO IRQ: {:?}", io_irq_input.get_level());
        right_motor_dir_output.set_level(if (loop_counter / 2) % 2 == 0 { Level::High } else { Level::Low }).unwrap();
        right_motor_pwm.set_duty(if loop_counter % 2 == 0 { 500 } else { 1000 }).unwrap();
        left_motor_dir_output.set_level(if (loop_counter / 2) % 2 == 0 { Level::Low } else { Level::High }).unwrap();
        log::info!("Emergency stop: {:?}", emergency_stop_input.get_level());
        enable_front_tof.set_level(if loop_counter % 2 == 0 { Level::High } else { Level::Low }).unwrap();
        left_motor_pwm.set_duty(if loop_counter % 2 == 0 { 500 } else { 1000 }).unwrap();
        log::info!("Conact right: {:?}", contact_right_input.get_level());
        log::info!("Gyro IRQ: {:?}", gyro_irq_input.get_level());
        log::info!("Left encoder value: {}", left_encoder.get_counter_value().unwrap());
        log::info!("Right encoder value: {}", right_encoder.get_counter_value().unwrap());
        
        let mut buf = [0x0F, 0x00];
        gyro_spi.transfer_in_place(&mut buf).unwrap();
        log::info!("Gyro WHO_AM_I read: {:?}(expected {:?})", buf[1], 0x6C);

        for addr in 1..=127 {
            match i2c_driver.read(addr as u8, &mut [0], TickType::new_millis(5).into()) {
                Ok(_) => log::info!("I2C device found at address 0x{:02X}", addr),
                Err(_) => (),
            }
        }

        std::thread::sleep(std::time::Duration::from_secs(500));
        loop_counter += 1;
    }
}
